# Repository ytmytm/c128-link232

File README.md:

These are boards for C128D/DCR internal WiFi modems based on the ACIA 6551 and Wemos D1 ESP8266 modules flashed with Zimodem firmware.

This work is heavily base on dabonetn's work from [Link232-Wifi](https://github.com/dabonetn/Link232-Wifi) project. Please go there for additional documentation.

# Installation

For both projects you need to decide on the interrupt source and address space. I recommend using `/NMI` as the interrupt and `$D700` as the base address.
This way, you can readily use most popular software for both C128 (DesTerm) and C64 (CCGMS), and the mod doesn't interfere with cartridges.

## Raise CIA

For both boards one of the CIA chips is raised to the daughterboard.

## Interrupt line

Both boards connect ACIA interrupt pin to local CIA chip but if it's not the right one (i.e. you want `/NMI` but the board is over CIA#1 which is connected to `/IRQ`) you need to run a wire to a suitable singal source from the mainboard.

## Base address

A signal for ACIA I/O address access in $D700-$D7FF area is readily available from U3 pin 12 that is otherwise unconnected.

## DotClock

Both boards require DotClock signal from the Expansion port pin 6.

# Swift-L (C128D)

This board is meant primarly for C128D and it is supposed to be plugged in place of CIA#2. It is a clone of [Link232 Swift-L](https://github.com/dabonetn/Link232-Wifi) project converted to Kicad6, with Burst connector added.

The `/NMI` signal is already available from the mainboard CIA#2 socket, so you only need to connect ACIA I/O signal and DotClock.

This board also features a 10-pin socket for a flat cable for burst connection to 1541 drives. The pinout is compatible with [DolphinDos3](https://e4aws.silverdr.com/projects/dolphindos3/) with `/FLAG` signal on pin 1, then 8 data lines and `/PC2` signal on pin 10. 

## C128DCR notes

There is not enough clearance under power supply on C128DCR to use that board with CIA#2, but this should fit in place of CIA#1.

You need to route `/NMI` interrupt line to pin 26 of ACIA 6551 somewhere from the board - the Expansion port pin D is the closet spot.

The burst connector would work correctly, but no software uses CIA#1 for that purpose.

## Swift-CIA3 (C128DCR)

This board is meant to be used in C128DCR over CIA#1. It has several features that I needed and you may find optional. If all you need is internal ACIA modem you should better use Swift-L variant.

You need to connect these external control signals to connector J1:

|pin|  |
|---|--|
|1|I/O signal for ACIA, for page $D700 connect to U3 pin 12|
|2|DotClock from Expansion port pin 6|
|3|Interrupt for ACIA, connect `/NMI` from Expansion port pin D|
|4|I/O signal for CIA#3 (optional)

In my case both ACIA I/O and CIA#3 I/O signals come from [U3 address decoder replaced by a GAL](https://github.com/ytmytm/c128-u3-replacement), so CIA#1 occupies addresses $DC00-$DC20 and CIA#3 appears in $DC20-$DC40

Connector J2 has a simple serial bus with GND/VCC/SP/CNT signals from CIA#3.

Connector J4 exposes CIA#3 port B so that it can be used to switch Kernal or Internal Function ROMs.

A jumper controls whether ACIA is connected to `/IRQ` (from CIA#1) or to `/NMI` (from J1 pin 3).

Another jumper selects 50/60Hz signal for TOD clock coming from ATTiny.

### CIA#3

CIA#3 is connected to ATA-IDE 40-pin connector for harddrives for [my CIAIDE project](https://github.com/ytmytm/c64-ciaide).
Port B lines are also connected to a pin header because they could be used for something like an internal ROM switcher.

### ATTiny85

There is a place for ATTiny85 to generate TOD clock signal.

In one of my C128DCRs I replaced power supply by a Mean Well RD35A power supply with 12V(1A)/5V(4A) rails. This runs much cooler than original power supply, but doesn't generate 9VAC. I don't mind the tape port as I don't use it anyway, but TOD clock is useful for GEOS.

Note that without 9VAC you need to replace CR8 by a wire (to short it to GND so that input to U16 pin 11 is not floating) and completely remove R7 and C80 elements.

**NOTE Don't use this sketch! Use the [more accurate code by fastjack](https://github.com/fastjack/attiny-clockgen)**

ATTiny runs this simple Arduino code to generate 50/60Hz waveform on TOD clock line, depending on jumper being open or closed:

```

// IDE: ATtiny25/45/85, internal 1MHz
// 1MHz is the default speed, no need to switch fuses to 8MHz
// compile to HEX (Sketch->Export compiled binary) and burn using TL866-II

// pinout
//   /RESET 1  U  8 5V
//   A3/PB3 2     7 A1/2/PB2
//   A2/PB4 3     6 PB1 PWM
//      GND 4     5 PB0 PWM -- output PWM 50Hz

const uint8_t PWM_pin = 0; // PB0, pin 5
const uint8_t mode_pin = 1; // PB1, pin 6 - jumper to GND for NTSC mode, keep floating (internal pullup) for PAL
uint8_t half_duty = 10;    // 10ms for PAL, 8ms for NTSC = 20ms/16ms

void setup() {
  pinMode(PWM_pin, OUTPUT);
  digitalWrite(PWM_pin, LOW);
  pinMode(mode_pin, INPUT_PULLUP);
  delay(200);
  if (digitalRead(mode_pin) == LOW) { // is it tied to GND?
    half_duty = 8;  // yes - switch to 8ms half duty cycle for 16ms ~ 62.5Hz frequency
  }
}

void loop() {
  // could be done using PWM and clock prescalers, but that is good enough for me
  while (true) {
    delay(half_duty); // 10ms - half of 20ms duty cycle
    digitalWrite(PWM_pin, HIGH);
    delay(half_duty); // 10ms - half of 20ms duty cycle
    digitalWrite(PWM_pin, LOW);
  }
}

```

# Zimodem - Wemos D1 firmware

Flash Wemos D1 with [Zimodem](https://github.com/bozimmerman/Zimodem) software.

I have compiled it with these settings:

Board: LOLIN(WEMOS) D1 R2 & Mini, 80MHz, flash 4MB (2MB FS, 1MB OTA), debug disabled, lwIP "v2 Lower Memory", Erase Flash: "Only sketch"

*Attention*: Check if this notice still exists in the README. If it does - make sure to downgrade Generic ESP8266 Library to version 2.7.4 in your Arduino IDE.

```
2.7.4 Arduino ESP8266 libraries using the Generic ESP8266 Module.  Versions newer than 2.7.4 may not work.
```

"May not work" in this case means that ESP8266 will keep crashing. You can test this still in Arduino IDE in the serial monitor.

*Attention*: Search for these defines and make these changes on the top of zimodem.ino before compiling:

1. Comment out this line to make RS232 lines non-inverted by default:
```
//# define RS232_INVERTED 1
```

2. Set default baud rate to 19200 (sensible choice for C64) or 38400 (maximum for ACIA)
```
#define DEFAULT_BAUD_RATE 19200
```

# C64/128 software

With these changes and ACIA setup to use `/NMI` at $D700 base address both latest version of CCGMS and DesTerm 128 will work fine.

Make sure that everything is setup correctly by issuing `AT` command. The modem should respond with `OK`.

Then start configuration menu by typing `AT+CONFIG`

By default RTS/CTS flow control is not enabled (so that operation can be checked in Arduino IDE serial monitor), so you should enable it with `ATF0` command because C64/128 will not keep up with scrolling the screen even in 19200 baud mode. You can save the settings to flash afterwards with `AT&W`.

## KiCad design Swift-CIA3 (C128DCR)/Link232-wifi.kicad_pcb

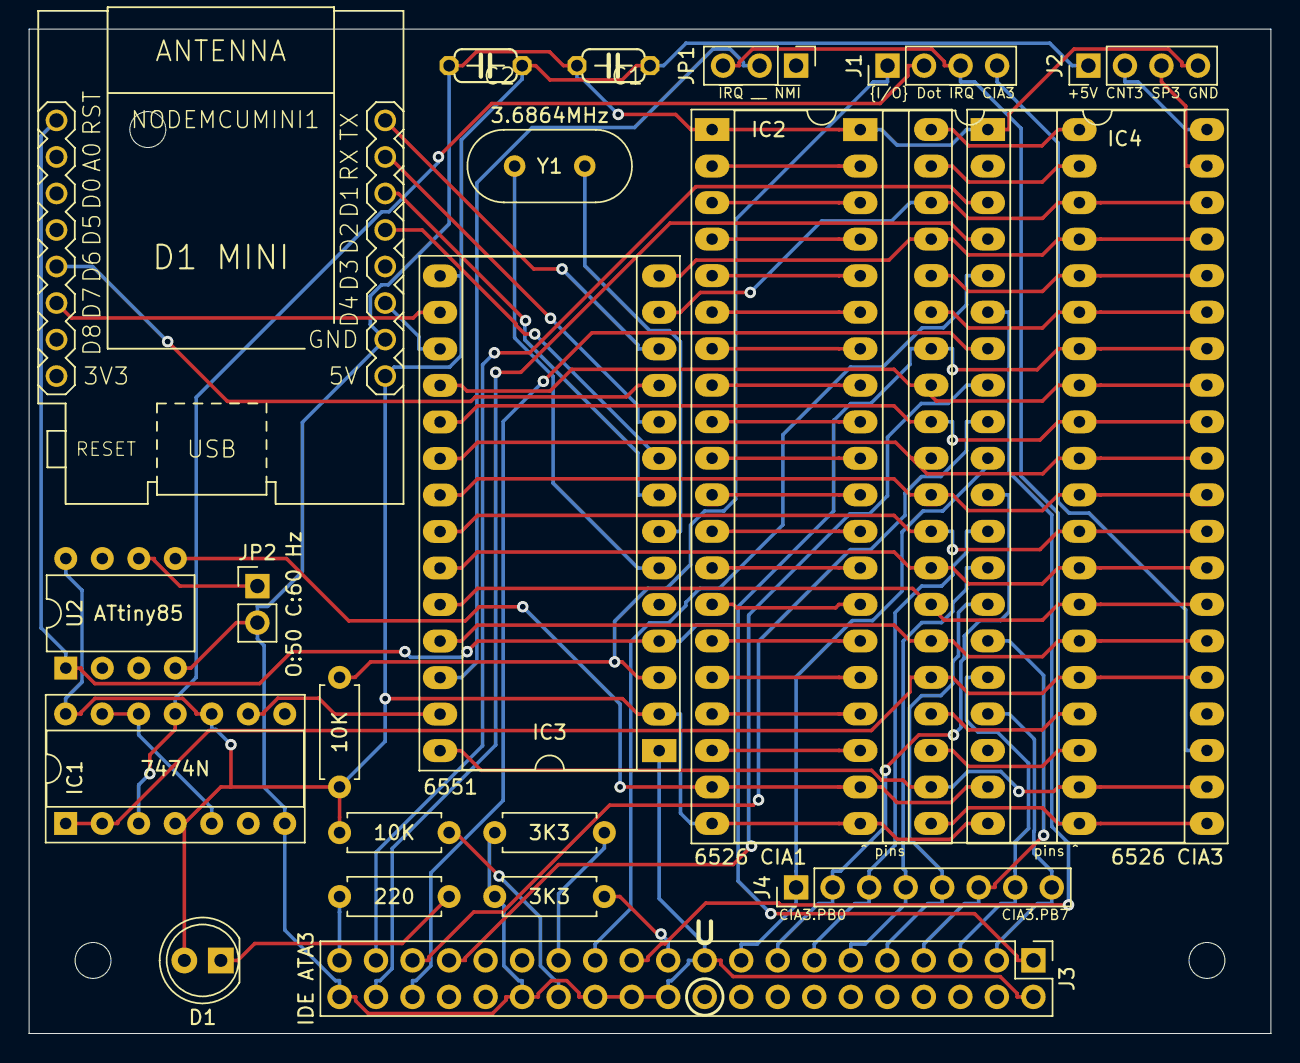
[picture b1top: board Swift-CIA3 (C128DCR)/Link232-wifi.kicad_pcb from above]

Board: 2 copper layers, 86.4 x 69.8 mm, 25 parts (0 on the bottom side), 78 nets.

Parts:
C1, C2: .1uf; C050-024X044
D1: LED; LED_D5.0mm
IC1: 7474N; DIP-14_W7.62mm_Socket
IC2: 6526 CIA1; DIP-40_W15.24mm_Socket_LongPads
IC3: 6551; DIP-28_W15.24mm_Socket_LongPads
IC4: 6526 CIA3; DIP-40_W15.24mm_Socket_LongPads
J1: {I/O} Dot ~{IRQ} ~{CIA3}; PinHeader_1x04_P2.54mm_Vertical
J2: +5V CNT3 SP3 GND; PinHeader_1x04_P2.54mm_Vertical
J3: IDE ATA3; PinHeader_2x20_P2.54mm_Vertical
J4: CIA3PB; PinHeader_1x08_P2.54mm_Vertical
JP1: ~{IRQ} __ ~{NMI}; PinHeader_1x03_P2.54mm_Vertical
JP2: O:50 C:60 Hz; PinHeader_1x02_P2.54mm_Vertical
NODEMCUMINI1: WEMOS-D1-MINI
R1, R5: 10K; R_Axial_DIN0207_L6.3mm_D2.5mm_P7.62mm_Horizontal
R2, R3: 3K3; R_Axial_DIN0207_L6.3mm_D2.5mm_P7.62mm_Horizontal
R4: 220; R_Axial_DIN0207_L6.3mm_D2.5mm_P7.62mm_Horizontal
REF1, REF2, REF3: MountingHole_2.5mm
U1: 6526 (pins to socket); DIP-40_W15.24mm_LongPads
U2: ATtiny85; DIP-8_W7.62mm
Y1: 3.6864MHz; Crystal_HC49-4H_Vertical

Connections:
+5V: C1.1, C2.1, D1.2 (A), IC1.4 (PRE), IC1.10 (PRE), IC1.14 (VCC), IC2.20 (VCC), IC3.2, IC3.15, IC4.20 (VCC), J2.1, NODEMCUMINI1.JP2.8 (5V), R1.1, R5.2, U1.20 (VCC), U2.8 (VCC)
/CNT: IC2.40 (CNT), U1.40 (CNT)
/CNT3: IC4.40 (CNT), J2.2
/CTS: IC3.9, NODEMCUMINI1.JP2.4 (D2)
/D0: IC2.33 (D0), IC3.18, IC4.33 (D0), U1.33 (D0)
/D1: IC2.32 (D1), IC3.19, IC4.32 (D1), U1.32 (D1)
/D2: IC2.31 (D2), IC3.20, IC4.31 (D2), U1.31 (D2)
/D3: IC2.30 (D3), IC3.21, IC4.30 (D3), U1.30 (D3)
/D4: IC2.29 (D4), IC3.22, IC4.29 (D4), U1.29 (D4)
/D5: IC2.28 (D5), IC3.23, IC4.28 (D5), U1.28 (D5)
/D6: IC2.27 (D6), IC3.24, IC4.27 (D6), U1.27 (D6)
/D7: IC2.26 (D7), IC3.25, IC4.26 (D7), U1.26 (D7)
/DCD: IC3.16, NODEMCUMINI1.JP1.6 (D7)
/DSR: IC3.17, NODEMCUMINI1.JP2.6 (D4)
/DTR: IC3.11, NODEMCUMINI1.JP1.5 (D6)
/DotClock: IC1.3 (CLK), IC1.11 (CLK), J1.2
/IDE.CSEL: J3.28, R5.1
/IDE.D0: IC4.10 (PB0), J3.17, J4.1
/IDE.D1: IC4.11 (PB1), J3.15, J4.2
/IDE.D2: IC4.12 (PB2), J3.13, J4.3
/IDE.D3: IC4.13 (PB3), J3.11, J4.4
/IDE.D4: IC4.14 (PB4), J3.9, J4.5
/IDE.D5: IC4.15 (PB5), J3.7, J4.6
/IDE.D6: IC4.16 (PB6), J3.5, J4.7
/IDE.D7: IC4.17 (PB7), J3.3, J4.8
/IDE.DA0: IC4.9 (PA7), J3.35
/IDE.DA1: IC4.8 (PA6), J3.33
/IDE.DA2: IC4.7 (PA5), J3.36
/IDE.DMARQ: J3.21, R2.2
/IDE.IORDY: J3.27, R3.2
/IDE.activity: J3.39, R4.2
/IDE.~CS0: IC4.3 (PA1), J3.37
/IDE.~CS1: IC4.4 (PA2), J3.38
/IDE.~IOR: IC4.5 (PA3), J3.25
/IDE.~IOW: IC4.6 (PA4), J3.23
/PA0: IC2.2 (PA0), U1.2 (PA0)
/PA1: IC2.3 (PA1), U1.3 (PA1)
/PA2: IC2.4 (PA2), U1.4 (PA2)
/PA3: IC2.5 (PA3), U1.5 (PA3)
/PA4: IC2.6 (PA4), U1.6 (PA4)
/PA5: IC2.7 (PA5), U1.7 (PA5)
/PA6: IC2.8 (PA6), U1.8 (PA6)
/PA7: IC2.9 (PA7), U1.9 (PA7)
/PB0: IC2.10 (PB0), U1.10 (PB0)
/PB1: IC2.11 (PB1), U1.11 (PB1)
/PB2: IC2.12 (PB2), U1.12 (PB2)
/PB3: IC2.13 (PB3), U1.13 (PB3)
/PB4: IC2.14 (PB4), U1.14 (PB4)
/PB5: IC2.15 (PB5), U1.15 (PB5)
/PB6: IC2.16 (PB6), U1.16 (PB6)
/PB7: IC2.17 (PB7), U1.17 (PB7)
/PHI2: IC1.1 (CLR), IC1.2 (D), IC2.25 (PHI2), IC4.25 (PHI2), U1.25 (PHI2)
/RS0: IC2.38 (RS0), IC3.13, IC4.38 (RS0), U1.38 (RS0)
/RS1: IC2.37 (RS1), IC3.14, IC4.37 (RS1), U1.37 (RS1)
/RS2: IC2.36 (RS2), IC4.36 (RS2), U1.36 (RS2)
/RS3: IC2.35 (RS3), IC4.35 (RS3), U1.35 (RS3)
/RTS: IC3.8, NODEMCUMINI1.JP2.3 (D1)
/RxD: IC3.12, NODEMCUMINI1.JP2.1 (TX)
/R/~W: IC2.22 (R/W), IC3.28, IC4.22 (R/W), U1.22 (R/W)
/SP: IC2.39 (SP), U1.39 (SP)
/SP3: IC4.39 (SP), J2.3
/TOD: IC2.19 (TOD), IC4.19 (TOD), U1.19 (TOD), U2.5 (AREF/PB0)
/TOD_50/~60: JP2.1, U2.6 (PB1)
/TxD: IC3.10, NODEMCUMINI1.JP2.2 (RX)
/~CIA3: IC4.23 (/CS), J1.4
/~CS: IC2.23 (/CS), U1.23 (/CS)
/~FLAG: IC2.24 (/FLAG), U1.24 (/FLAG)
/~IRQB: IC3.26, JP1.2
/~IRQ: IC2.21 (/IRQ), IC4.21 (/IRQ), J1.3, JP1.3, U1.21 (/IRQ)
/~I/O: IC3.3, J1.1, R1.2
/~PC: IC2.18 (/PC), U1.18 (/PC)
/~RESET: IC2.34 (/RES), IC3.4, IC4.34 (/RES), J3.1, NODEMCUMINI1.JP1.1 (RST), U1.34 (/RES), U2.1 (~RESET/PB5)
GND: C1.2, C2.2, IC1.7 (GND), IC2.1 (GND), IC3.1, IC4.1 (GND), J2.4, J3.2, J3.19, J3.22, J3.24, J3.26, J3.30, J3.40, JP2.2, NODEMCUMINI1.JP2.7 (GND), R2.1, R3.1, U1.1 (GND), U2.4 (GND)
unnamed: D1.1 (K), R4.1
unnamed: IC1.9 (Q), IC3.27
unnamed: IC1.5 (Q), IC1.12 (D), IC1.13 (CLR)
unnamed: IC3.6, Y1.2
unnamed: IC3.7, Y1.1

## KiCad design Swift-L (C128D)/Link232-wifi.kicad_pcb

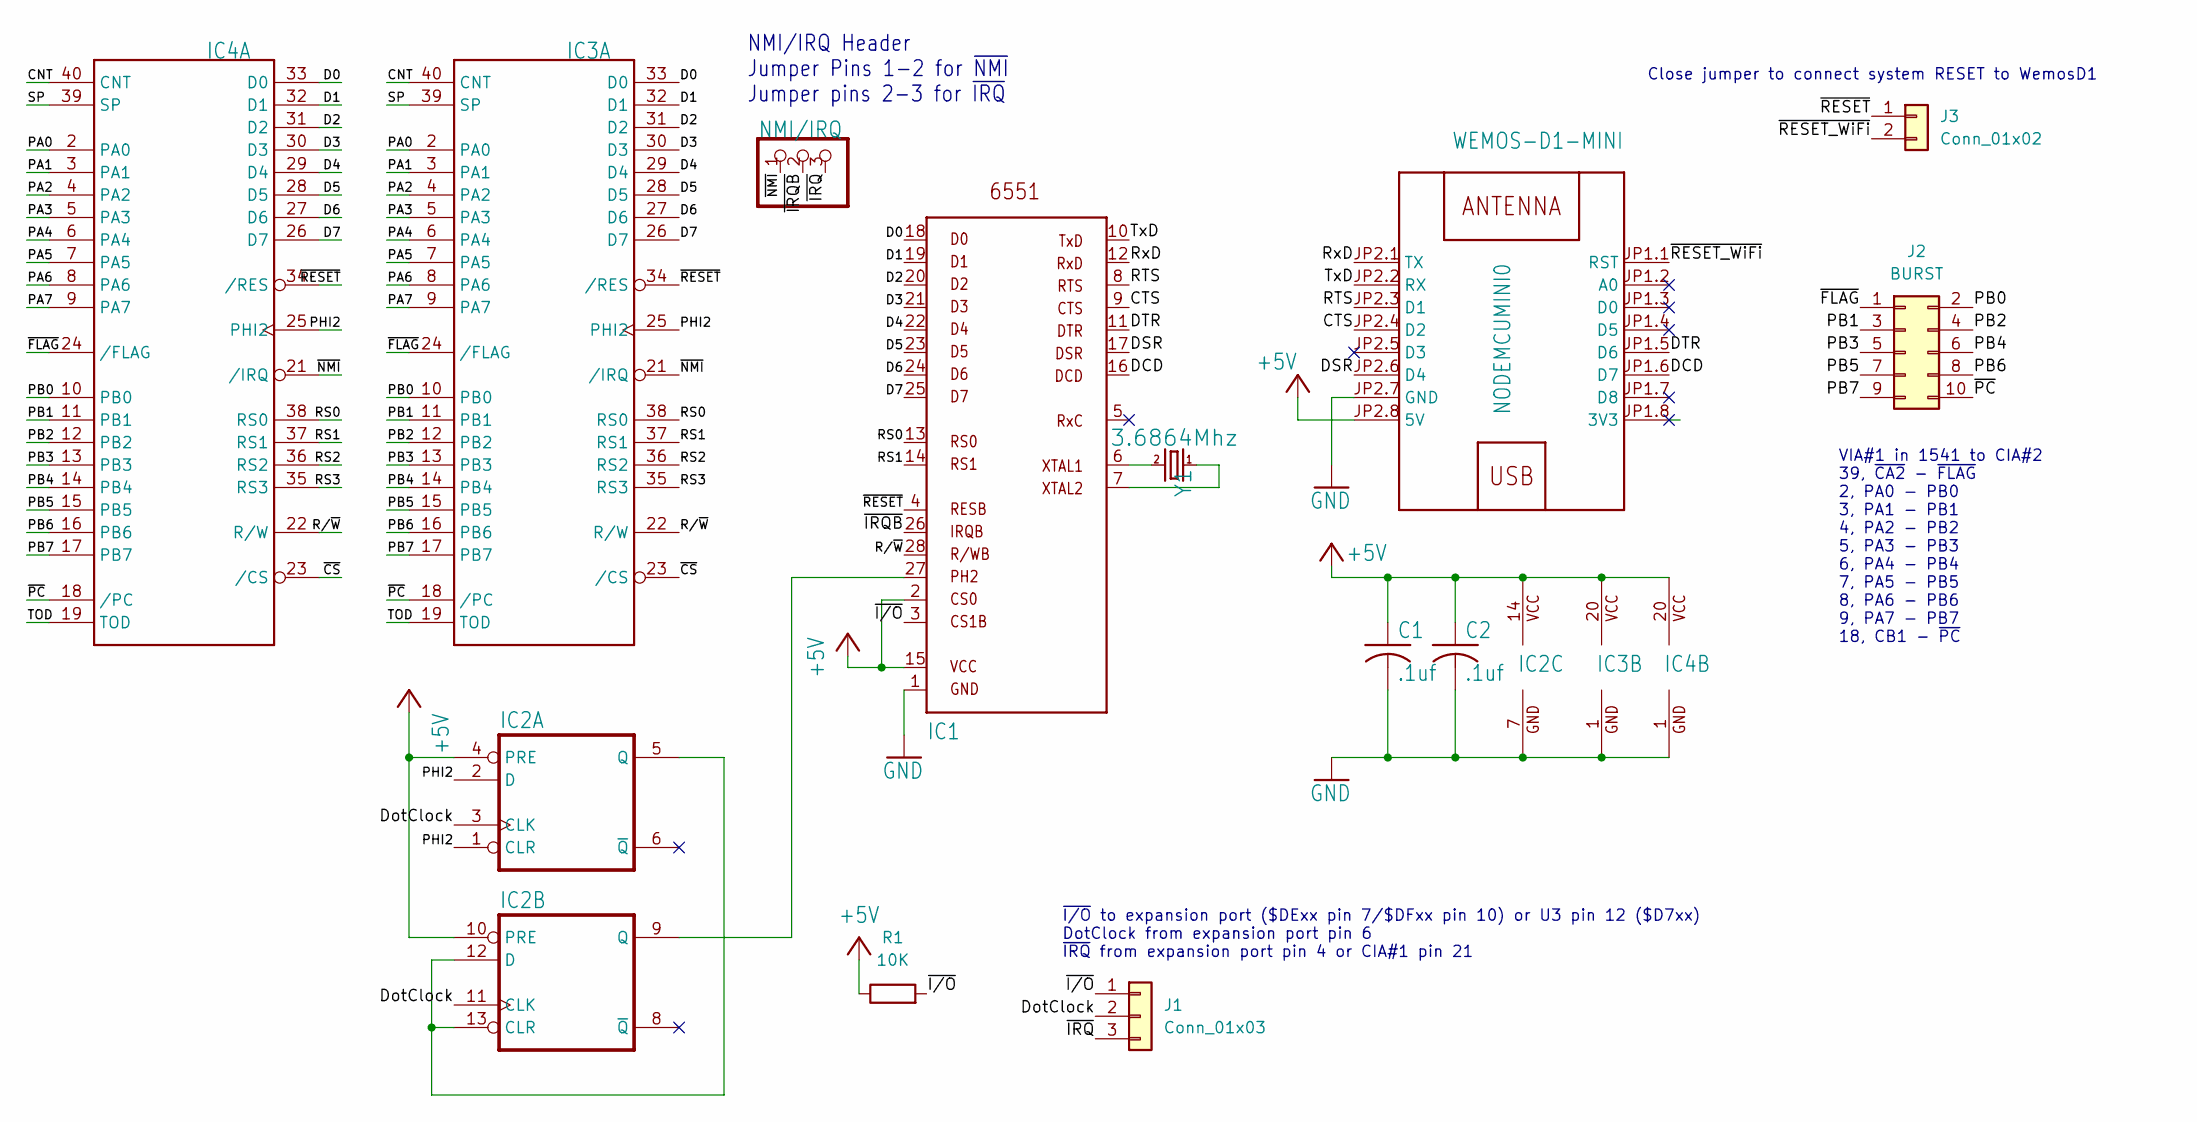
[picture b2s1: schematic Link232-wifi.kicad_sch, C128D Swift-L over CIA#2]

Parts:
C1, C2: .1uf; C050-024X044
IC1: 6551; DIP-28_W15.24mm_Socket_LongPads
IC2: 7474N; DIP-14_W7.62mm_Socket_LongPads
IC3: 6526; DIP-40_W15.24mm_Socket_LongPads
IC4: 6526; DIP-40_W15.24mm_LongPads
J1: Conn_01x03; PinHeader_1x03_P2.54mm_Vertical
J2: BURST; PinHeader_2x05_P2.54mm_Vertical
J3: Conn_01x02; PinHeader_1x02_P2.54mm_Vertical
JP1: NMI/IRQ; PinHeader_1x03_P2.54mm_Vertical
NODEMCUMINI0: WEMOS-D1-MINI
R1: 10K; R_Axial_DIN0207_L6.3mm_D2.5mm_P10.16mm_Horizontal
Y1: 3.6864Mhz; Crystal_HC49-4H_Vertical

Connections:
+5V: C1.1, C2.1, IC1.2, IC1.15, IC2.4 (PRE), IC2.10 (PRE), IC2.14 (VCC), IC3.20 (VCC), IC4.20 (VCC), NODEMCUMINI0.JP2.8 (5V), R1.1
/CNT: IC3.40 (CNT), IC4.40 (CNT)
/CTS: IC1.9, NODEMCUMINI0.JP2.4 (D2)
/D0: IC1.18, IC3.33 (D0), IC4.33 (D0)
/D1: IC1.19, IC3.32 (D1), IC4.32 (D1)
/D2: IC1.20, IC3.31 (D2), IC4.31 (D2)
/D3: IC1.21, IC3.30 (D3), IC4.30 (D3)
/D4: IC1.22, IC3.29 (D4), IC4.29 (D4)
/D5: IC1.23, IC3.28 (D5), IC4.28 (D5)
/D6: IC1.24, IC3.27 (D6), IC4.27 (D6)
/D7: IC1.25, IC3.26 (D7), IC4.26 (D7)
/DCD: IC1.16, NODEMCUMINI0.JP1.6 (D7)
/DSR: IC1.17, NODEMCUMINI0.JP2.6 (D4)
/DTR: IC1.11, NODEMCUMINI0.JP1.5 (D6)
/DotClock: IC2.3 (CLK), IC2.11 (CLK), J1.2
/PA0: IC3.2 (PA0), IC4.2 (PA0)
/PA1: IC3.3 (PA1), IC4.3 (PA1)
/PA2: IC3.4 (PA2), IC4.4 (PA2)
/PA3: IC3.5 (PA3), IC4.5 (PA3)
/PA4: IC3.6 (PA4), IC4.6 (PA4)
/PA5: IC3.7 (PA5), IC4.7 (PA5)
/PA6: IC3.8 (PA6), IC4.8 (PA6)
/PA7: IC3.9 (PA7), IC4.9 (PA7)
/PB0: IC3.10 (PB0), IC4.10 (PB0), J2.2
/PB1: IC3.11 (PB1), IC4.11 (PB1), J2.3
/PB2: IC3.12 (PB2), IC4.12 (PB2), J2.4
/PB3: IC3.13 (PB3), IC4.13 (PB3), J2.5
/PB4: IC3.14 (PB4), IC4.14 (PB4), J2.6
/PB5: IC3.15 (PB5), IC4.15 (PB5), J2.7
/PB6: IC3.16 (PB6), IC4.16 (PB6), J2.8
/PB7: IC3.17 (PB7), IC4.17 (PB7), J2.9
/PHI2: IC2.1 (CLR), IC2.2 (D), IC3.25 (PHI2), IC4.25 (PHI2)
/RS0: IC1.13, IC3.38 (RS0), IC4.38 (RS0)
/RS1: IC1.14, IC3.37 (RS1), IC4.37 (RS1)
/RS2: IC3.36 (RS2), IC4.36 (RS2)
/RS3: IC3.35 (RS3), IC4.35 (RS3)
/RTS: IC1.8, NODEMCUMINI0.JP2.3 (D1)
/RxD: IC1.12, NODEMCUMINI0.JP2.1 (TX)
/R/~W: IC1.28, IC3.22 (R/W), IC4.22 (R/W)
/SP: IC3.39 (SP), IC4.39 (SP)
/TOD: IC3.19 (TOD), IC4.19 (TOD)
/TxD: IC1.10, NODEMCUMINI0.JP2.2 (RX)
/~CS: IC3.23 (/CS), IC4.23 (/CS)
/~FLAG: IC3.24 (/FLAG), IC4.24 (/FLAG), J2.1
/~IRQB: IC1.26, JP1.2
/~IRQ: J1.3, JP1.3
/~I/O: IC1.3, J1.1, R1.2
/~NMI: IC3.21 (/IRQ), IC4.21 (/IRQ), JP1.1
/~PC: IC3.18 (/PC), IC4.18 (/PC), J2.10
/~RESET_WiFi: J3.2, NODEMCUMINI0.JP1.1 (RST)
/~RESET: IC1.4, IC3.34 (/RES), IC4.34 (/RES), J3.1
GND: C1.2, C2.2, IC1.1, IC2.7 (GND), IC3.1 (GND), IC4.1 (GND), NODEMCUMINI0.JP2.7 (GND)
unnamed: IC1.6, Y1.2
unnamed: IC1.7, Y1.1
unnamed: IC1.27, IC2.9 (Q)
unnamed: IC2.5 (Q), IC2.12 (D), IC2.13 (CLR)

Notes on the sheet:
NMI/IRQ Header Jumper Pins 1-2 for ~{NMI} Jumper pins 2-3 for ~{IRQ}
Close jumper to connect system RESET to WemosD1
~{I/O} to expansion port ($DExx pin 7/$DFxx pin 10) or U3 pin 12 ($D7xx) DotClock from expansion port pin 6 ~{IRQ} from expansion port pin 4 or CIA#1 pin 21
VIA#1 in 1541 to CIA#2 39, ~{CA2} - ~{FLAG} 2, PA0 - PB0 3, PA1 - PB1 4, PA2 - PB2 5, PA3 - PB3 6, PA4 - PB4 7, PA5 - PB5 8, PA6 - PB6 9, PA7 - PB7 18, CB1 - ~{PC}

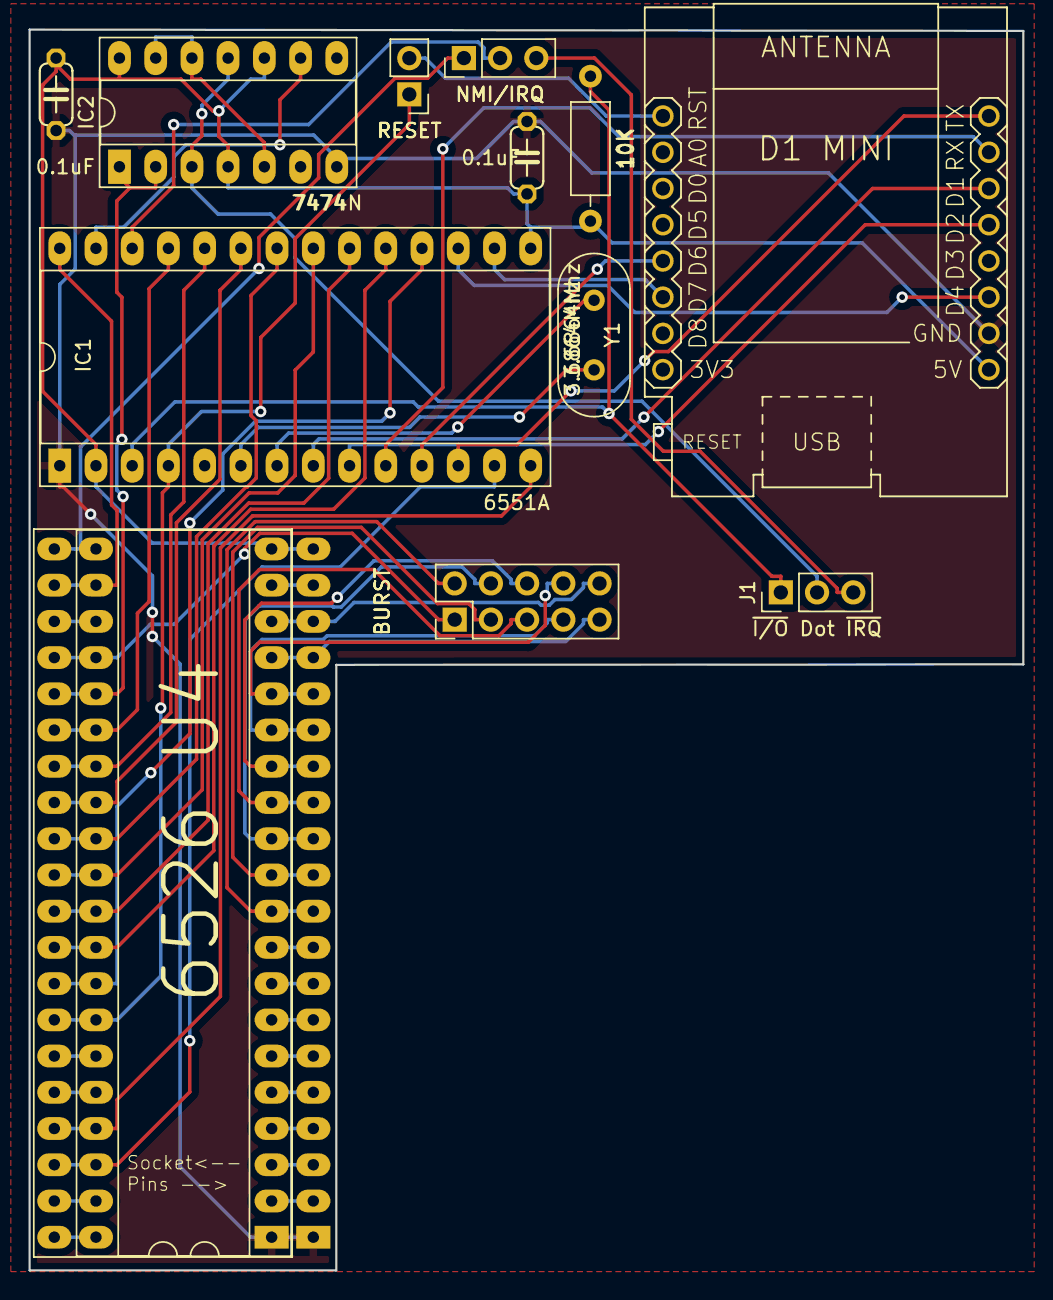
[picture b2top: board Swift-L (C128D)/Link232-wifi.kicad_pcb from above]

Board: 2 copper layers, 69.7 x 87.0 mm, 13 parts (0 on the bottom side), 56 nets.

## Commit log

2023-04-09 import of Kicad 6.0 projects
2025-04-23 Update README.md with link to fastjack's attiny clock code
